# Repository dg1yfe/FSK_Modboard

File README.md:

# FSK_Modboard
A little amplifier board for Demodulator &amp; Modulator access in Motorola MC micro transceivers 

The board provides uses a dual OP-Amp to do the following:

1) Transmit Path
   - Provide an external input for direct (wide-band) modulator access
   - Amplify the signal supplied via the external input by a factor of 2.7
   - Add microphone audio signal and (amplified) external signal and route the mix to the modulator
     (be sure to disconnect or mute your microphone when using the external input)
 
2) Receive Path
   - Pick-up the demodulated signal right after the demodulator and amplify it by 10
   - Provide the amplified signal (amplitude about ~500 mV) at an external output

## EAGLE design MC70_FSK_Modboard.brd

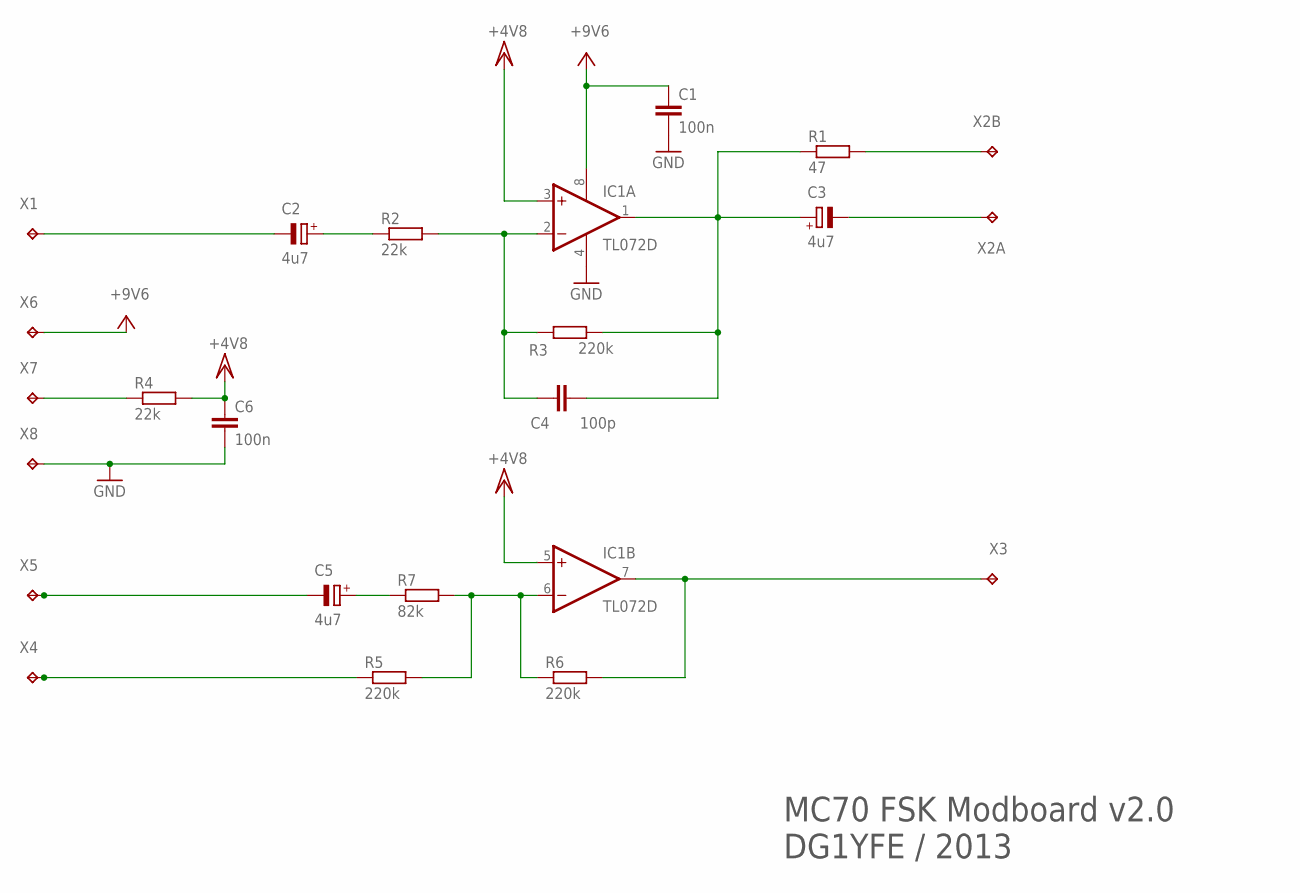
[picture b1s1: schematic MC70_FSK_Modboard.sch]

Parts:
C1, C6: 100n; C0805
C2, C3, C5: 4u7; A/3216-18R
C4: 100p; C0805
IC1: TL072D; SO08
R1: 47; R0805
R2, R4: 22k; R0805
R3, R5, R6: 220k; R0805
R7: 82k; R0805
X1, X2A, X2B, X3, X4, X5, X6, X7, X8: TPTP15R; TP15R

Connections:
GND: C1.2, C6.2, IC1.4 (V-), X8.TP
unnamed: IC1.7 (OUT), R6.2, X3.TP
unnamed: R5.1, X4.TP
unnamed: IC1.6 (-IN), R5.2, R6.1, R7.2
unnamed: C5.+, R7.1
unnamed: C5.-, X5.TP
unnamed: C2.-, X1.TP
unnamed: C2.+, R2.1
unnamed: R4.1, X7.TP
unnamed: C4.2, IC1.2 (-IN), R2.2, R3.1
unnamed: C3.+, C4.1, IC1.1 (OUT), R1.1, R3.2
unnamed: C3.-, X2A.TP
unnamed: R1.2, X2B.TP
VCC: C1.1, IC1.8 (V+), X6.TP
VCC/2: C6.1, IC1.3 (+IN), IC1.5 (+IN), R4.2

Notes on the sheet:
MC70 FSK Modboard v2.0 DG1YFE / 2013

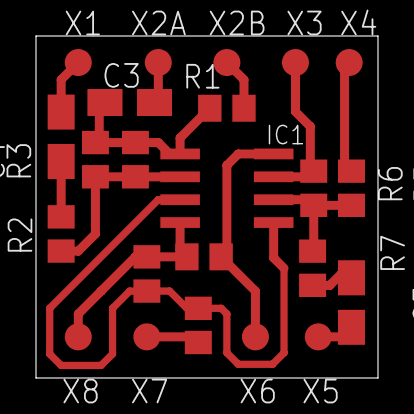
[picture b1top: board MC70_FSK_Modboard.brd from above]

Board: 2 copper layers, 19.0 x 19.0 mm, 23 parts (0 on the bottom side), 15 nets.

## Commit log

2013-03-12 Modboard 2.0
2017-02-04 Doku auf Stand gebracht und ins Repo gepackt
